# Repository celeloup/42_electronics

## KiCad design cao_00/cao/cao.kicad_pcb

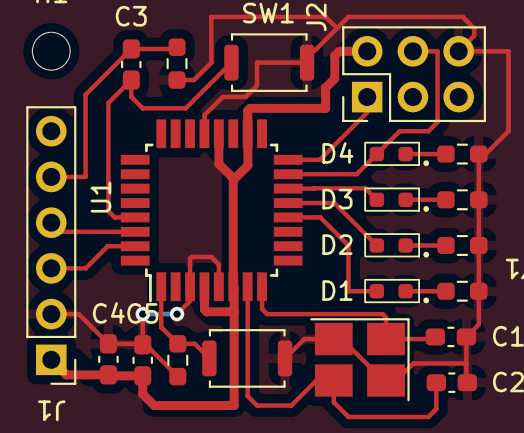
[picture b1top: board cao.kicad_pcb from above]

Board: 2 copper layers, 22 parts (0 on the bottom side), 19 nets.

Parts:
C1, C2: 22pF; C_0603
C3, C4: 100nF; C_0603
C5: 10uF; C_0603
D1, D2, D3, D4: LED; LED_0603
H1: MountingHole; MountingHole_2.1mm
J1: Conn_01x06
J2: AVR-ISP-6
R1, R2: 10K; R
R3, R4, R5, R6: 330R; R
SW1, SW2: SW_Push; SW_PUSH
U1: ATmega328P-AU; ATMEGA328P_AU
Y1: 16MHz; CRISTAL_16MH

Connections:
+5V: C4.1, C5.2, J1.1, J2.2 (VCC), U1.4 (VCC), U1.6 (VCC), U1.18 (AVCC), U1.20 (AREF)
/BUT_0: R2.2, SW2.1, U1.1 (PD3)
/LED_0: D1.2 (A), U1.12 (PB0)
/LED_1: D2.2 (A), U1.13 (PB1)
/LED_2: D3.2 (A), U1.14 (PB2)
/LED_3: D4.2 (A), J2.4 (MOSI), U1.15 (PB3)
/MCU_RX: J1.4, U1.30 (PD0)
/MCU_TX: J1.3, U1.31 (PD1)
/MISO: J2.1 (MISO), U1.16 (PB4)
/SCK: J2.3 (SCK), U1.17 (PB5)
/XTAL1: C2.1, U1.7 (XTAL1/PB6), Y1.3
/XTAL2: C1.2, U1.8 (XTAL2/PB7), Y1.1
/~RESET: C3.2, J2.5 (~RST), SW1.1, U1.29 (~RESET/PC6)
GND: C1.1, C2.2, C4.2, C5.1, J1.2, J2.6 (GND), R1.2, R2.1, R3.2, R4.2, R5.2, R6.2, SW1.2, SW2.2, U1.3 (GND), U1.5 (GND), U1.21 (GND), Y1.2, Y1.4
unnamed: C3.1, J1.5, R1.1
unnamed: D1.1 (K), R3.1
unnamed: D2.1 (K), R4.1
unnamed: D3.1 (K), R5.1
unnamed: D4.1 (K), R6.1

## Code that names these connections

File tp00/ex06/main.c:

#ifndef __AVR_ATmega328P__
#define __AVR_ATmega328P__
#endif

#include <avr/io.h>

#define DEBOUCE_DELAY 50000

int main()
{
    DDRB = 0xFF;
    unsigned char last_state = PIND & (1 << PD3);
    int counter = 0;

    for(;;)
    {
        unsigned char new_state = PIND & (1 << PD3);
        if (last_state != new_state)
        {
            if (new_state == 0)
            {
                if (counter < 15)
                    counter++;
                else
                    counter = 0;
                PORTB = 0;
                PORTB = counter & ((1 << PB3) | (1 << PB2) | (1 << PB1) | (1 << PB0));
            }
				
			for (long i = 0; i < DEBOUCE_DELAY; i++)
            {}
			last_state = new_state;
        }
    }
    return (0);
}

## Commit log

2022-01-10 the code speaks for itself
2022-01-11 moved exs in tp00, finished ex05 and 06
2022-01-11 moved files
2022-01-11 ex00 timer good, ex01 in progress
2022-01-12 fixed defines, ex01 of tp01, ex00 of tp02 and first half of ex01 tp02
2022-01-13 tp03 ex00 write z via USART
2022-01-13 tp03 ex01 done
2022-01-13 tp03 ex02 read ok
2022-01-13 tp03 ex03 switch case ok
2022-01-13 tp03 ex04 login baby
2022-01-13 finished tp02/ex00 the bastard
2022-01-16 Rush rush baby
2022-01-17 renamed folders to match subject name
2022-01-17 writing in EEPROM yay (tech_00, ex01)
2022-01-17 rush update
2022-01-17 added ex02 tech00 dump eeprom
2022-01-17 removed white space, added exclude .bin .hex
2022-01-18 restored the missing interrupt function and modified to work on new button position
2022-01-18 Modified ex01 to make it compatible new circuit (PD3 to PD2) and finished ex02
2022-01-18 i can light up a rgb led, i am boss
2022-01-18 First half of ex02 done, missing parsing
2022-01-19 I can read the potentiometre
2022-01-19 hot hot hot
2022-01-19 missing exercice is back
2022-01-19 turning back in time
2022-01-19 I CAN CONTROL THE LIGHT
2022-01-19 removed useless line
2022-01-19 FINISH
2022-01-25 my beautiful schema
2022-01-26 added footprint
2022-01-31 last backup
